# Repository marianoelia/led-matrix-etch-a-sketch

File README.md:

# LED Matrix Digital Etch-A-Sketch
## Introduction
The idea of this project was to make an etch a sketch using a 8x32 led matrix, 2 potentiometers, and an accelerometer to erase the screen!

Parts Used: <br>
Arduino Uno <br>
8x32 Matrix with 4 embedded MAX7219 Controller Chips <br>
2 Linear Potentiometers <br>
12V to 5V Buck Converter <br>
ADXL335 Sparkfun Accelerometer Breakout Board <br>
Pre-sensitized Copper Board as the PCB <br>

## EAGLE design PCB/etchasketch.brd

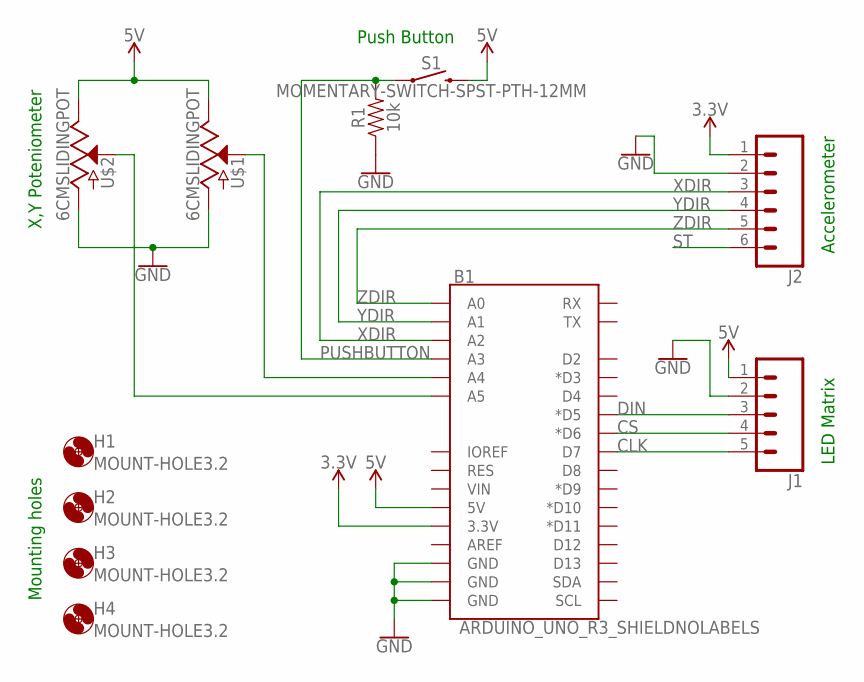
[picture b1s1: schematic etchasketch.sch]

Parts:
B1: ARDUINO_UNO_R3_SHIELDNOLABELS; UNO_R3_SHIELD_NOLABELS
H1, H2, H3, H4: MOUNT-HOLE3.2; 3,2
J1: CONN_05NO_SILK; 1X05_NO_SILK
J2: CONN_06NO_SILK_NO_POP; 1X06_NO_SILK
R1: 10k; AXIAL-0.3
S1: MOMENTARY-SWITCH-SPST-PTH-12MM; TACTILE_SWITCH_PTH_12MM
U$1, U$2: 6CMSLIDINGPOT; SLIDINGPOT

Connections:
3.3V: B1.3.3V, J2.1
5V: B1.5V, J1.1, S1.3 (2), U$1.P$3 (E), U$2.P$3 (E)
CLK: B1.D7, J1.5
CS: B1.D6 (*D6), J1.4
DIN: B1.D5 (*D5), J1.3
GND: B1.GND@0 (GND), B1.GND@1 (GND), B1.GND@2 (GND), J1.2, J2.2, R1.P$1 (1), U$1.P$1 (A), U$2.P$1 (A)
unnamed: B1.A4, U$1.P$2 (S)
unnamed: B1.A5, U$2.P$2 (S)
PUSHBUTTON: B1.A3, R1.P$2 (2), S1.1
ST: J2.6
XDIR: B1.A2, J2.3
YDIR: B1.A1, J2.4
ZDIR: B1.A0, J2.5

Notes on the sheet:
Accelerometer
LED Matrix
X,Y Poteniometer
Mounting holes
Push Button

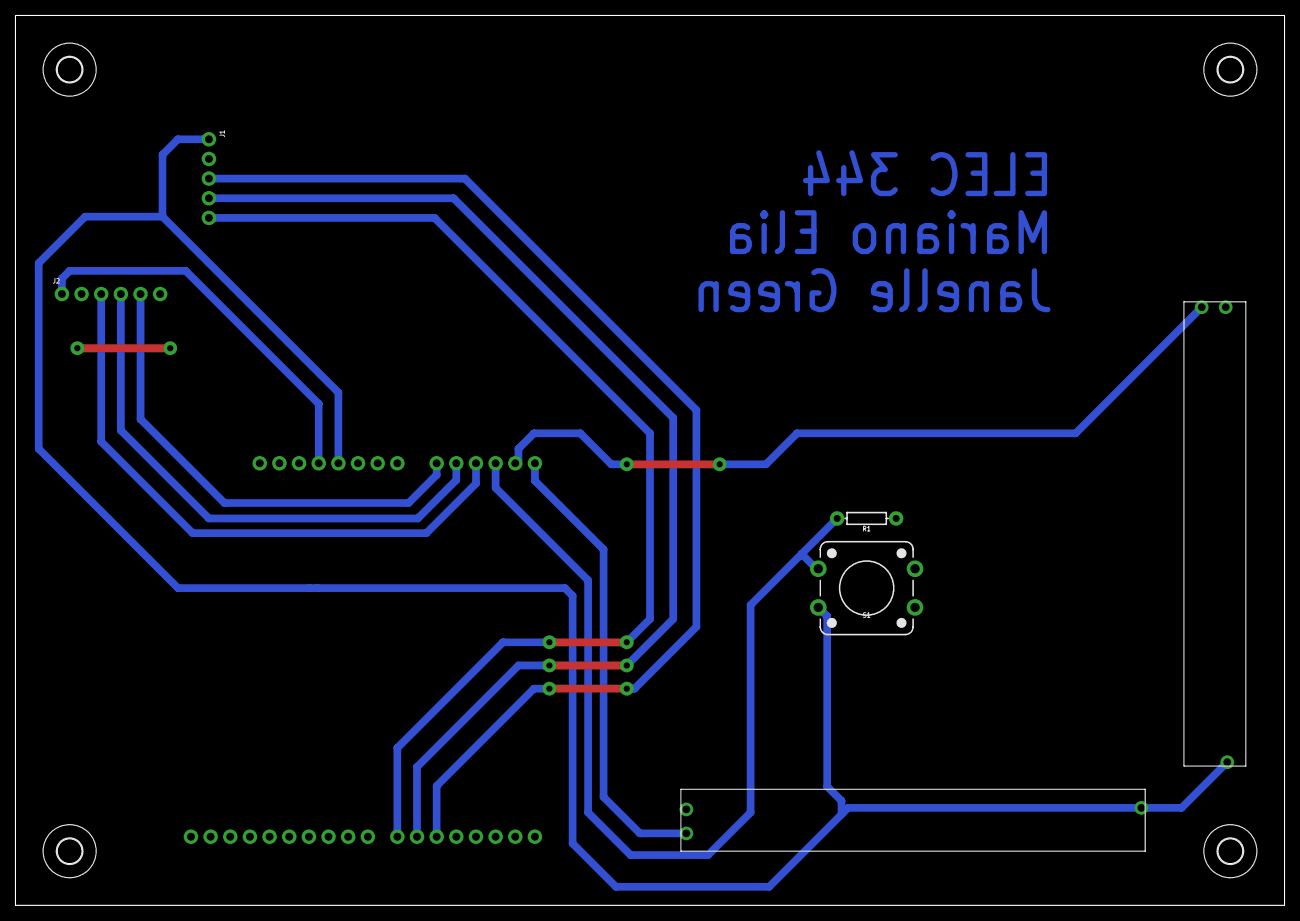
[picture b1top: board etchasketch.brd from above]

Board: 2 copper layers, 164.0 x 115.0 mm, 11 parts (1 on the bottom side), 12 nets.

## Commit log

2018-11-10 Added PCB files
2018-11-10 PCB etched
2018-11-15 Add firmware files
2018-11-15 Make schematic neater
2018-12-01 Added comments to code
2018-12-01 Modifiy traces
2018-12-03 Organized schematic
2018-12-20 update gitignore
2018-12-20 remove old files

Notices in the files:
parts and their libraries:
SparkFun-Boards: Licensing: Creative Commons ShareAlike 4.0 International - https://creativecommons.org/licenses/by-sa/4.0
